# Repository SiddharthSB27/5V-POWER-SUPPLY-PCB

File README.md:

# 5V Power Supply PCB

## Overview
PCB design of a regulated 5V power supply circuit.
The schematic and PCB layout were designed in KiCad
and verified using DRC and 3D PCB view.

## Tools Used
- KiCad

## Project Status
✔ Schematic completed  
✔ PCB file created  
✔ PCB layout in progress  

## Images

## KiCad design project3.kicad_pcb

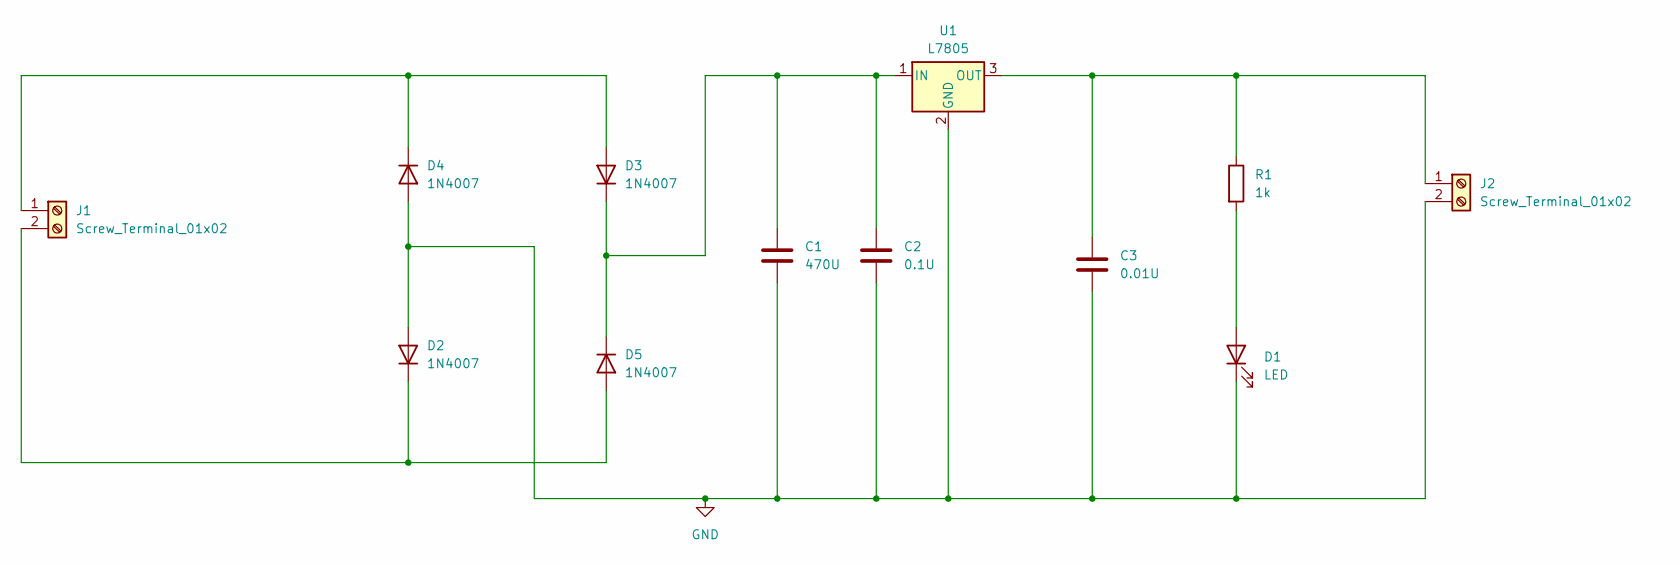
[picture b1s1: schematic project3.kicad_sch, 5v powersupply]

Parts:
C1: 470U; CP_Axial_L10.0mm_D6.0mm_P15.00mm_Horizontal
C2: 0.1U; CP_Radial_D4.0mm_P1.50mm
C3: 0.01U; CP_Radial_D4.0mm_P1.50mm
D1: LED; LED_D3.0mm_Horizontal_O1.27mm_Z6.0mm
D2, D3, D4, D5: 1N4007; D_DO-15_P2.54mm_Vertical_AnodeUp
J1, J2: Screw_Terminal_01x02; PinSocket_1x02_P2.00mm_Vertical
R1: 1k; R_Axial_DIN0204_L3.6mm_D1.6mm_P5.08mm_Horizontal
U1: L7805; TO-220-3_Vertical

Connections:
GND: C1.2, C2.2, C3.2, D1.1 (K), D2.2 (A), D4.2 (A), J2.2, U1.2 (GND)
unnamed: D1.2 (A), R1.2
unnamed: D2.1 (K), D5.2 (A), J1.2
unnamed: D3.2 (A), D4.1 (K), J1.1
unnamed: C1.1, C2.1, D3.1 (K), D5.1 (K), U1.1 (IN)
unnamed: C3.1, J2.1, R1.1, U1.3 (OUT)

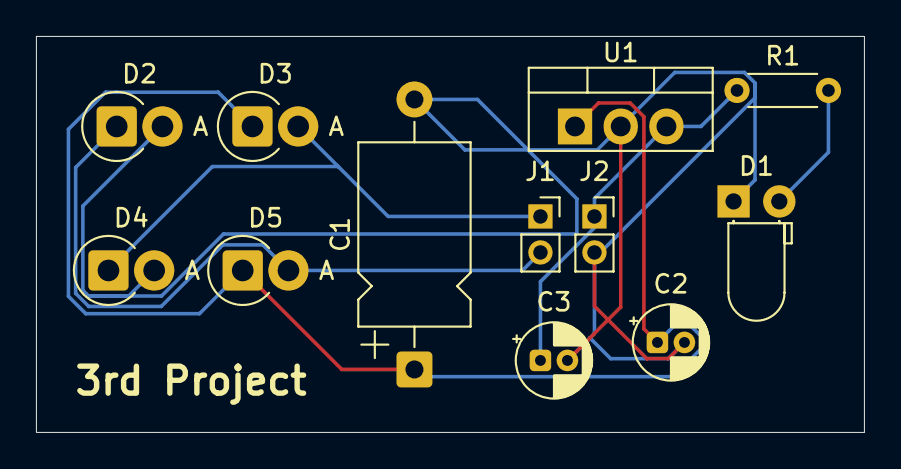
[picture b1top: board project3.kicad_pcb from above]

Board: 2 copper layers, 46.0 x 22.0 mm, 12 parts (0 on the bottom side), 6 nets.

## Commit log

2025-12-25 Rename Screenshot 2025-12-25 183816.png to images/schematic.png
2025-12-25 Rename Screenshot 2025-12-25 183903.png to images/pcb.png
2025-12-25 Rename Screenshot 2025-12-25 183939.png to images/3dview.png
2026-03-02 Rename project3.kicad_prl to KICAD/project3.kicad_prl
2026-03-02 Rename project3.kicad_pro to KICAD/project3.kicad_pro
2026-03-28 Created using Colab
